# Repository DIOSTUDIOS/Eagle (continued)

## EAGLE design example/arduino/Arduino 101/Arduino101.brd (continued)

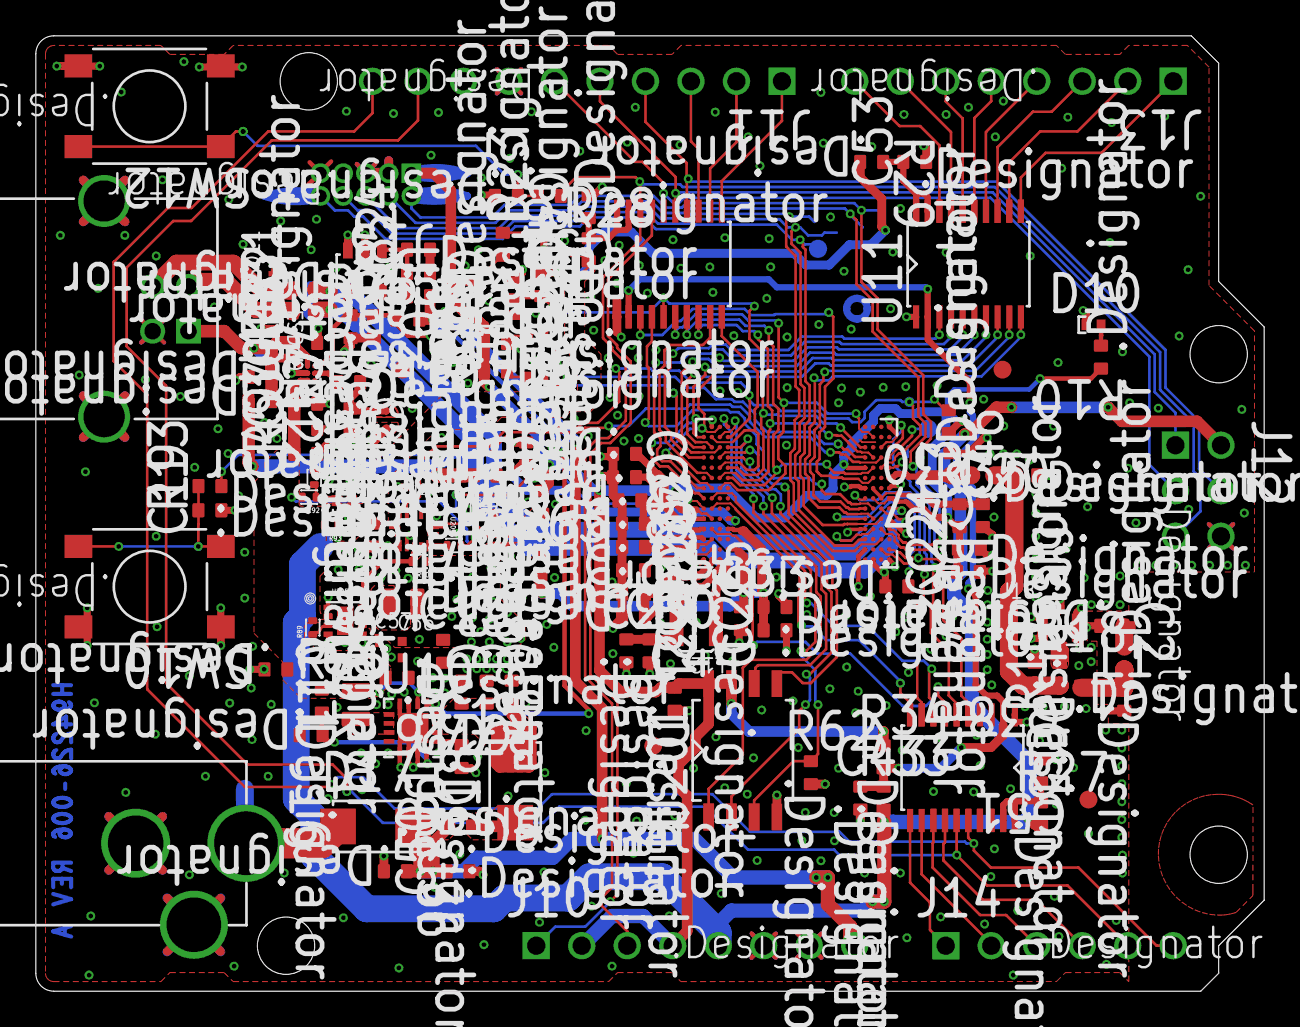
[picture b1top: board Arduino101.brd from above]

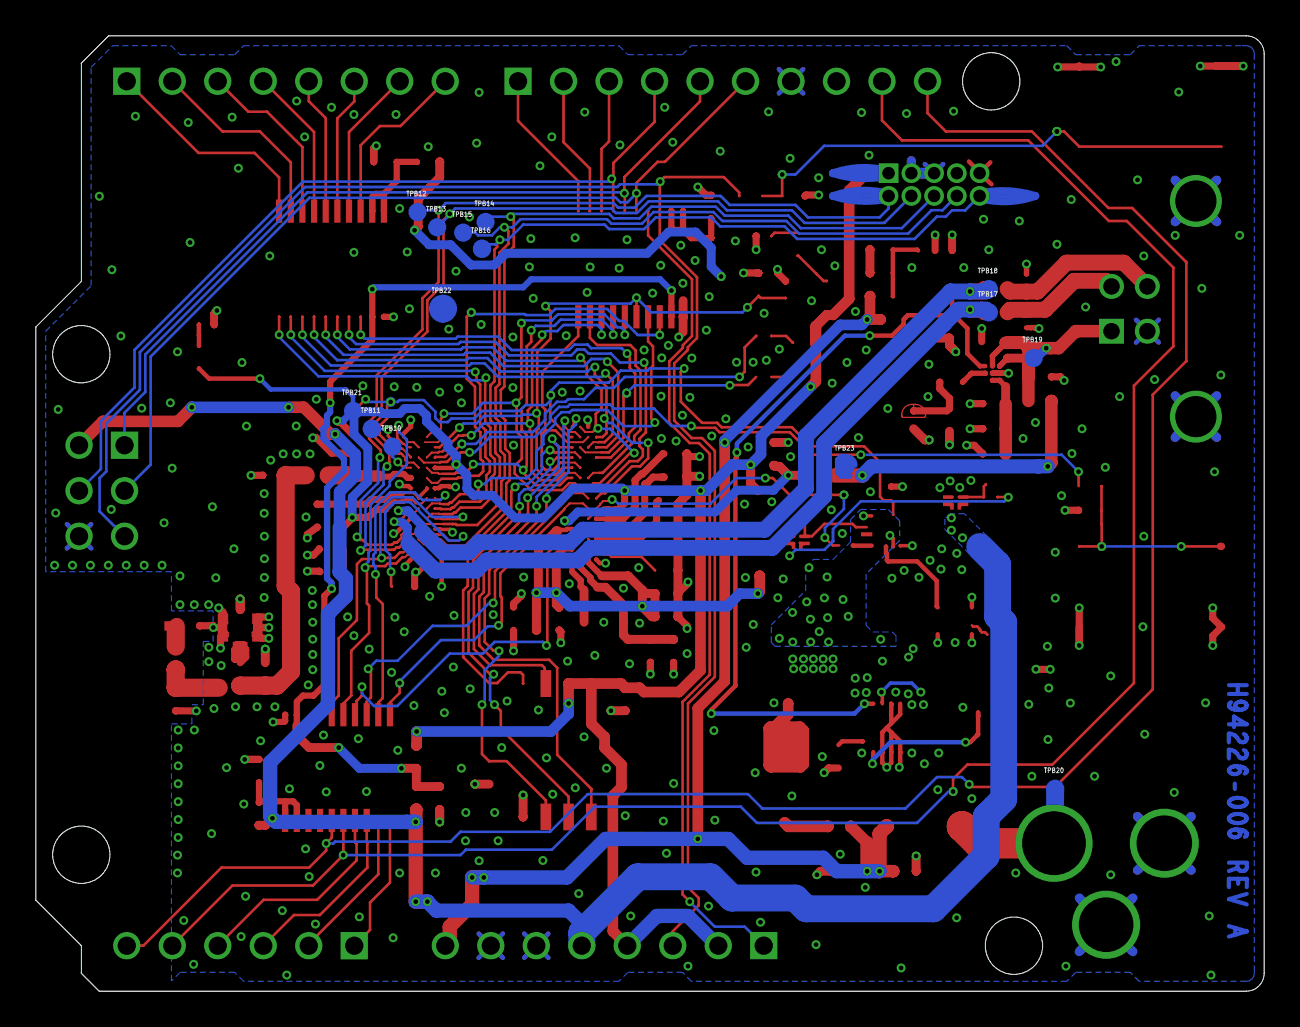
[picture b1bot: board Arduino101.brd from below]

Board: 6 copper layers, 68.6 x 53.3 mm, 146 parts (14 on the bottom side), 117 nets.

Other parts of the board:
DRILEGEND: DRILEGEND

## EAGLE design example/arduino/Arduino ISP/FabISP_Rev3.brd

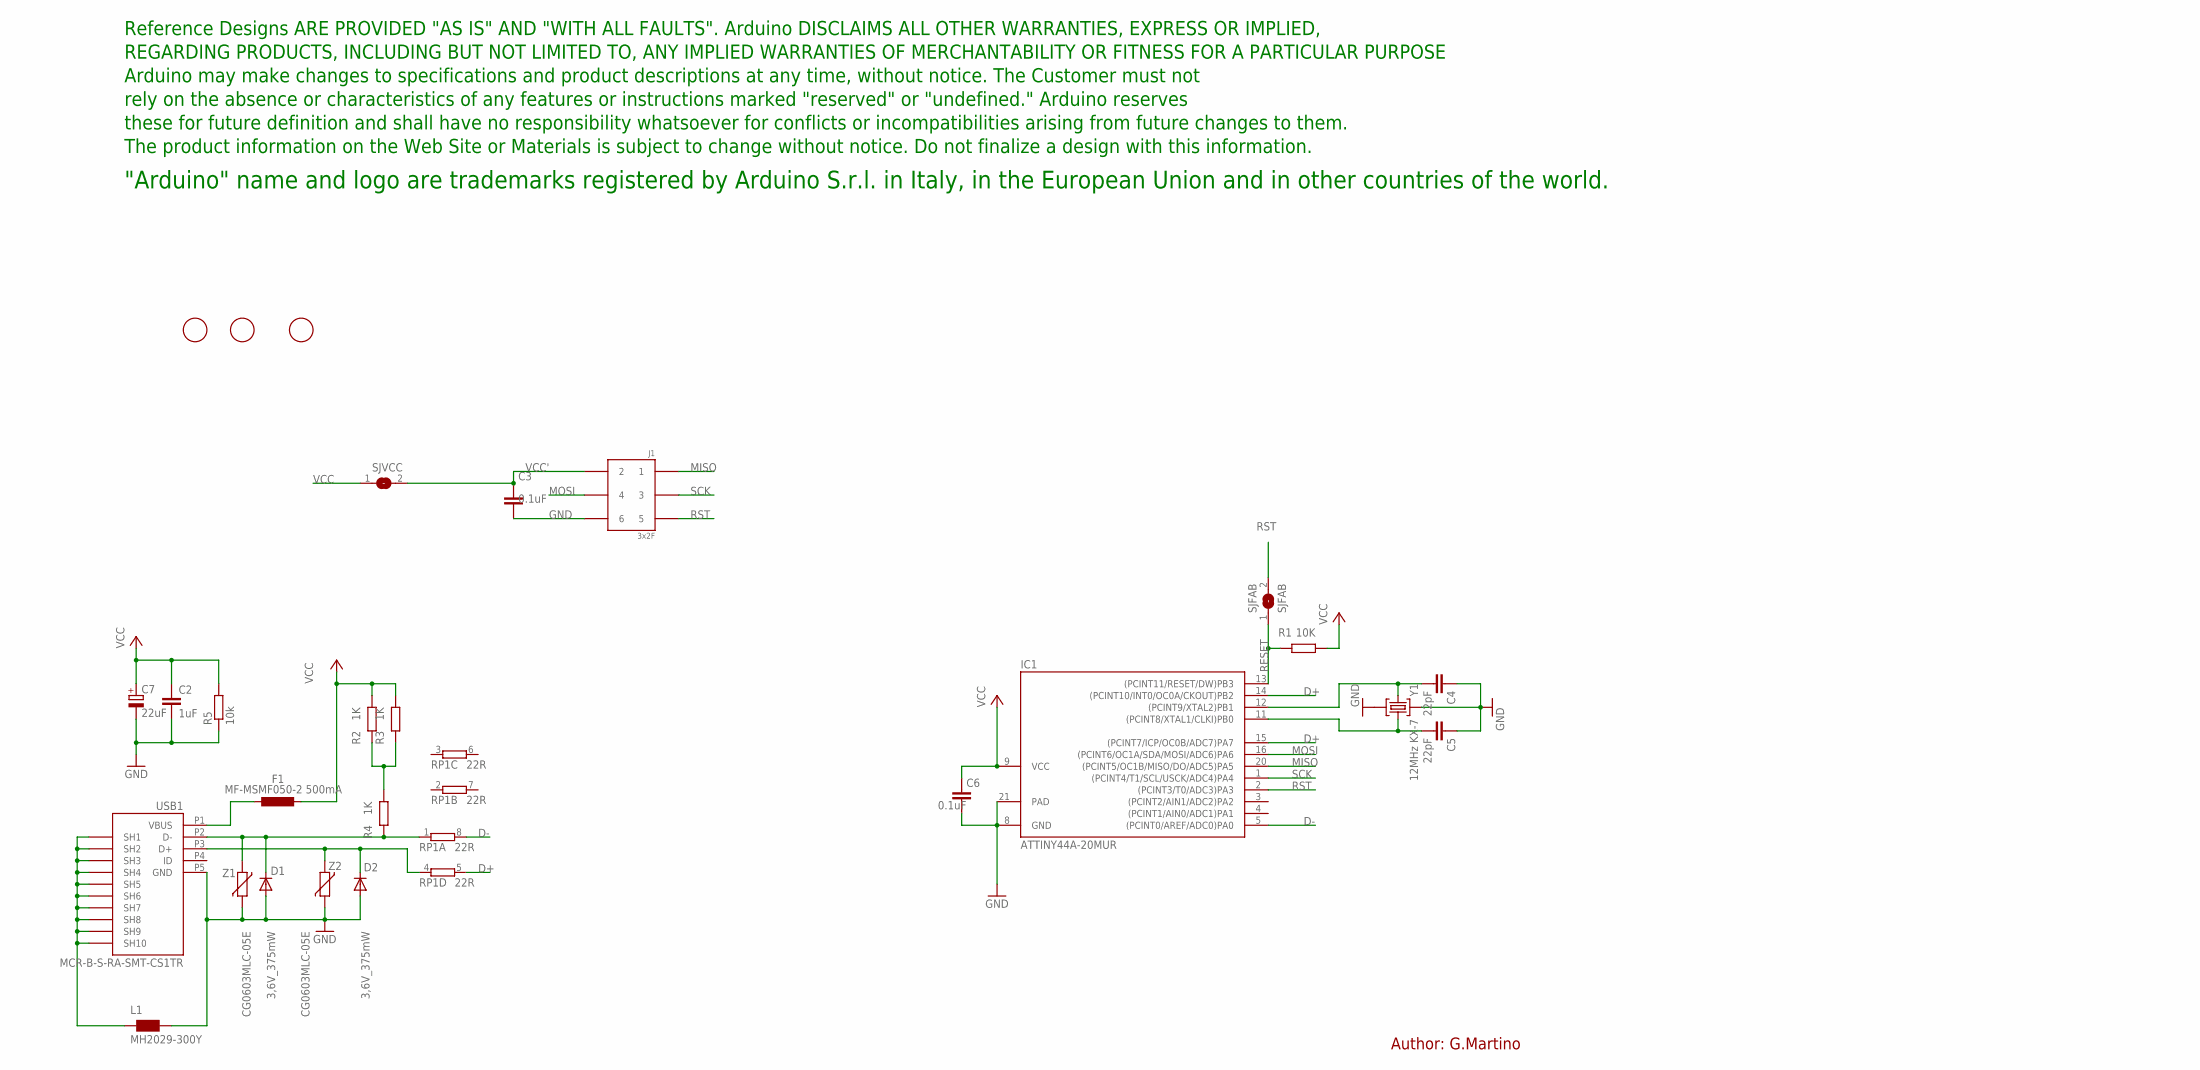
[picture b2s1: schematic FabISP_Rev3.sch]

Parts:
C2: 1uF; C0402
C3, C6: 0.1uF; C0402
C4, C5: 22pF; C0402
C7: 22uF; SMC_B
D1, D2: 3,6V_375mW; SOD123
F1: MF-MSMF050-2 500mA; L1812
IC1: ATTINY44A-20MUR; ATTINY24_44_84_QFN/MLF20
J1: 3x2F; HEAD3X2
L1: MH2029-300Y; 0805
R1: 10K; R0402
R2, R3, R4: 1K; R0402
R5: 10k; R0603-ROUND
RP1: 22R; CAY16
SJFAB: SJFAB
SJVCC: SJFAB
U$1, U$2, U$3: FIDUCIALMOUNT; FIDUCIA-MOUNT
U$5: DISCLAIMER
USB1: MCR-B-S-RA-SMT-CS1TR; CON2_USB_MICRO_B_AT
Y1: 12MHz KX-7; CRYSTAL-3.2-2.5
Z1, Z2: CG0603MLC-05E; CT/CN0603

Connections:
D+: IC1.14 ((PCINT10/INT0/OC0A/CKOUT)PB2), IC1.15 ((PCINT7/ICP/OC0B/ADC7)PA7), RP1.5 (2)
D-: IC1.5 ((PCINT0/AREF/ADC0)PA0), RP1.8 (2)
GND: C2.2, C3.2, C4.1, C5.1, C6.2, C7.-, D1.A, D2.A, IC1.8 (GND), IC1.21 (PAD), J1.6, L1.2, R5.1, USB1.P5 (GND), Y1.2 (GND), Y1.4 (GND), Z1.1, Z2.1
MISO: IC1.20 ((PCINT5/OC1B/MISO/DO/ADC5)PA5), J1.1
MOSI: IC1.16 ((PCINT6/OC1A/SDA/MOSI/ADC6)PA6), J1.4
unnamed: D1.C, R4.1, RP1.1, USB1.P2 (D-), Z1.2
unnamed: D2.C, RP1.4 (1), USB1.P3 (D+), Z2.2
unnamed: R2.1, R3.1, R4.2
unnamed: L1.1, USB1.P$1 (SH7), USB1.P$2 (SH8), USB1.P$3 (SH9), USB1.P$4 (SH10), USB1.P$5 (SH7), USB1.P$6 (SH8), USB1.P$7 (SH9), USB1.P$8 (SH10), USB1.S1 (SH1), USB1.S2 (SH2), USB1.S3 (SH3), USB1.S4 (SH4), USB1.S5 (SH5), USB1.S6 (SH6)
unnamed: F1.2, USB1.P1 (VBUS)
RESET: IC1.13 ((PCINT11/RESET/DW)PB3), R1.1, SJFAB.1
RST: IC1.2 ((PCINT3/T0/ADC3)PA3), J1.5, SJFAB.2
SCK: IC1.1 ((PCINT4/T1/SCL/USCK/ADC4)PA4), J1.3
VCC: C2.1, C6.1, C7.+, F1.1, IC1.9 (VCC), R1.2, R2.2, R3.2, R5.2, SJVCC.1
VCC': C3.1, J1.2, SJVCC.2
XTAL1: C4.2, IC1.12 ((PCINT9/XTAL2)PB1), Y1.3 (C2)
XTAL2: C5.2, IC1.11 ((PCINT8/XTAL1/CLKI)PB0), Y1.1 (C1)

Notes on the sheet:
Author: G.Martino

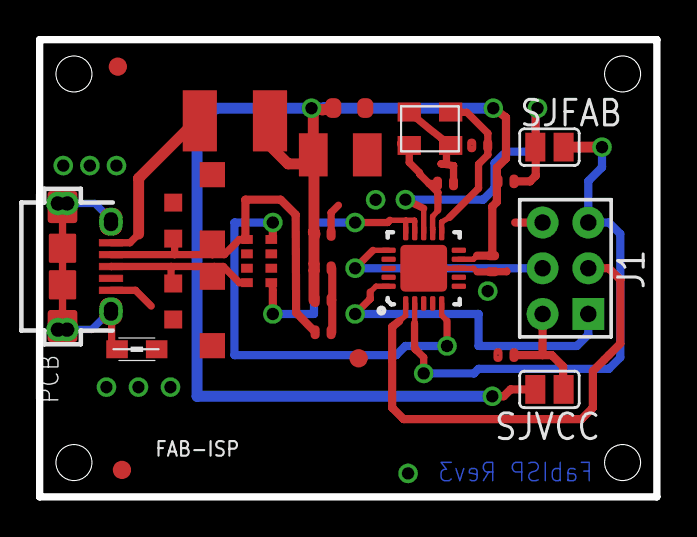
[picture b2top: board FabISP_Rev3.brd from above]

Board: 2 copper layers, 34.3 x 25.4 mm, 28 parts (0 on the bottom side), 17 nets.

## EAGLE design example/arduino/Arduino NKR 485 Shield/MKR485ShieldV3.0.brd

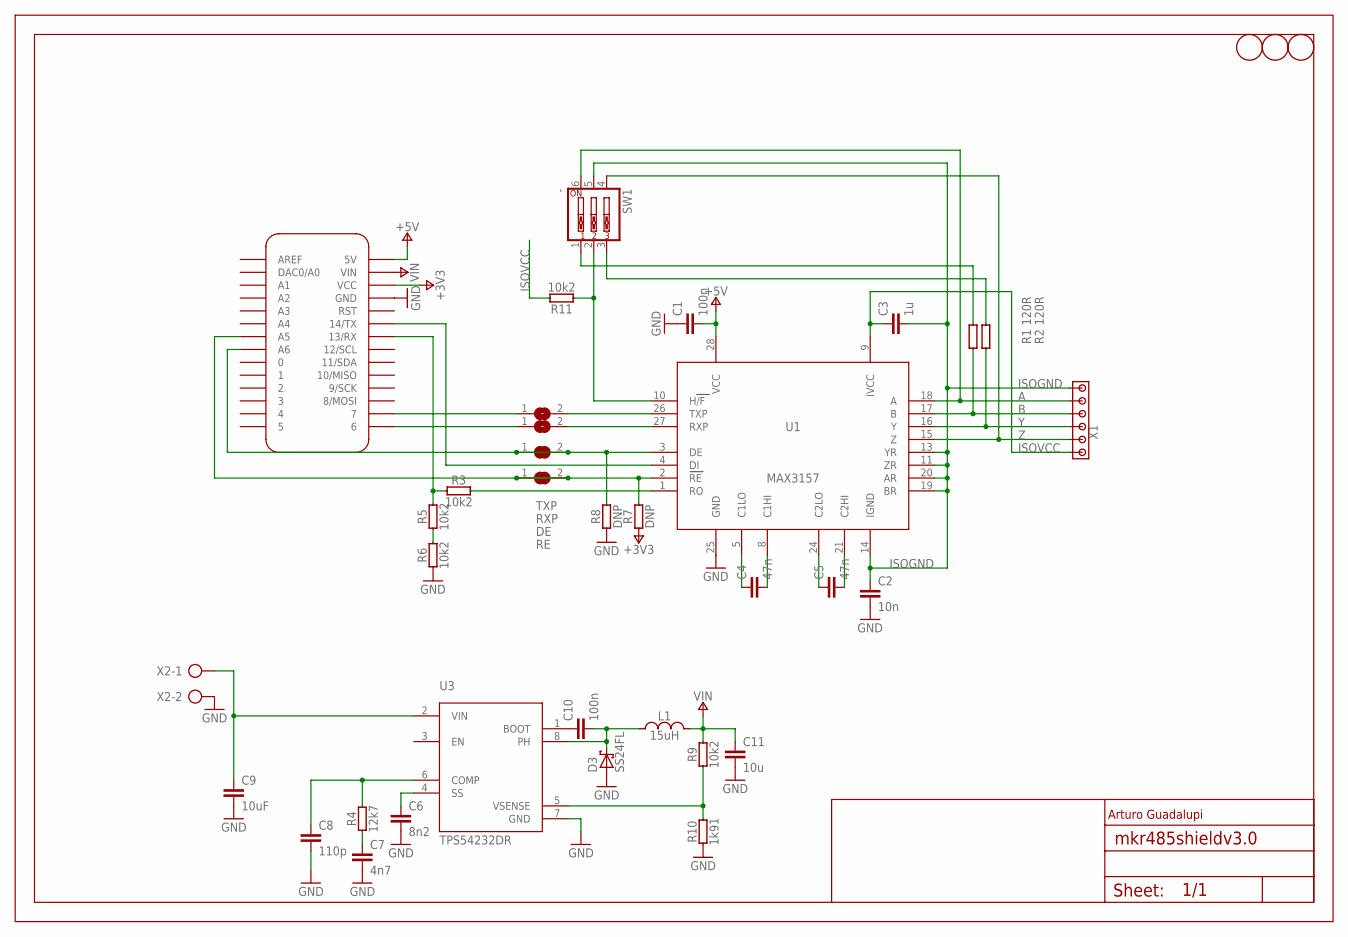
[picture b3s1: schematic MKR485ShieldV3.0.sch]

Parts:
C1, C10: 100n; 0402-1005X55N
C2: 10n; 0603-1608X90N
C3: 1u; 0603-1608X90N
C4, C5: 47n; 0402-1005X55N
C6: 8n2; 0402-1005X55N
C7: 4n7; 0402-1005X55N
C8: 110p; 0402-1005X55N
C9: 10uF; C1206
C11: 10u; 0603-1608X90N
D3: SS24FL; SOD123F
DE: DNP; SJ
FD1, FD2, FD3: DNP; FD-1-1.5
FRAME1: DNP; FRAME
L1: 15uH; SRN6045
MKR1: DNP; MKRBOARD-DIM
R1, R2: 120R; 0402-1005X55N
R3, R5, R6, R9, R11: 10k2; 0402-1005X55N
R4: 12k7; 0402-1005X55N
R7, R8: DNP; 0402-1005X55N
R10: 1k91; 0402-1005X55N
RE: DNP; SJ
RXP: DNP; SJ
SW1: -; EDG-03
TXP: DNP; SJ
U1: MAX3157; TSSOP28
U3: TPS54232DR; SO08
X1: -; SCREW6X2.54
X2: -; AK300/2

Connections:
+3V3: MKR1.VCC, R7.1
+5V: C1.2, MKR1.5V, U1.28 (VCC)
A: SW1.6, U1.18 (A), X1.5
B: R1.1, U1.17 (B), X1.4
DE: DE.1, DE.2, MKR1.A6, R8.2, U1.3 (DE)
GND: C1.1, C2.2, C6.2, C7.2, C8.2, C9.2, C11.2, D3.A, MKR1.GND, R6.1, R8.1, R10.1, U1.25 (GND), U3.7 (GND), X2.2
ISOGND: C2.1, C3.2, SW1.5, U1.11 (ZR), U1.13 (YR), U1.14 (IGND), U1.19 (BR), U1.20 (AR), X1.6
ISOVCC: C3.1, R11.2, U1.9 (IVCC), X1.1
unnamed: TXP.2, U1.26 (TXP)
unnamed: RXP.2, U1.27 (RXP)
unnamed: R11.1, SW1.2, U1.10 (H/F)
unnamed: R2.2, SW1.3
unnamed: MKR1.14 (14/TX), U1.4 (DI)
unnamed: C4.1, U1.5 (C1LO)
unnamed: C4.2, U1.8 (C1HI)
unnamed: C5.1, U1.24 (C2LO)
unnamed: C5.2, U1.21 (C2HI)
unnamed: C7.1, R4.1
unnamed: C8.1, R4.2, U3.6 (COMP)
unnamed: MKR1.13 (13/RX), R3.1, R5.2
unnamed: R1.2, SW1.1
unnamed: C6.1, U3.4 (SS)
unnamed: R3.2, U1.1 (RO)
unnamed: C9.1, U3.2 (VIN), X2.1
unnamed: C10.1, U3.1 (BOOT)
unnamed: C10.2, D3.C, L1.1, U3.8 (PH)
unnamed: R9.1, R10.2, U3.5 (VSENSE)
unnamed: R5.1, R6.2
RE: MKR1.A5, R7.2, RE.1, RE.2, U1.2 (RE)
RXP: MKR1.6, RXP.1
TXP: MKR1.7, TXP.1
VIN: C11.1, L1.2, MKR1.VIN, R9.2
Y: R2.1, U1.16 (Y), X1.3
Z: SW1.4, U1.15 (Z), X1.2

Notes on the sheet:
Arturo Guadalupi

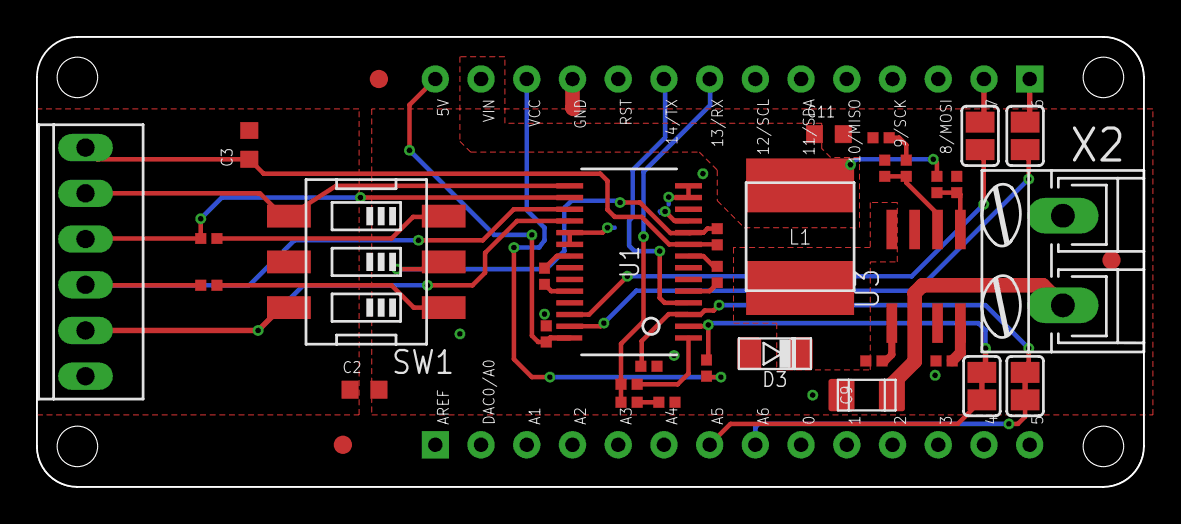
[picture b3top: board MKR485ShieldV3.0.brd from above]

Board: 2 copper layers, 61.5 x 25.0 mm, 38 parts (0 on the bottom side), 34 nets.

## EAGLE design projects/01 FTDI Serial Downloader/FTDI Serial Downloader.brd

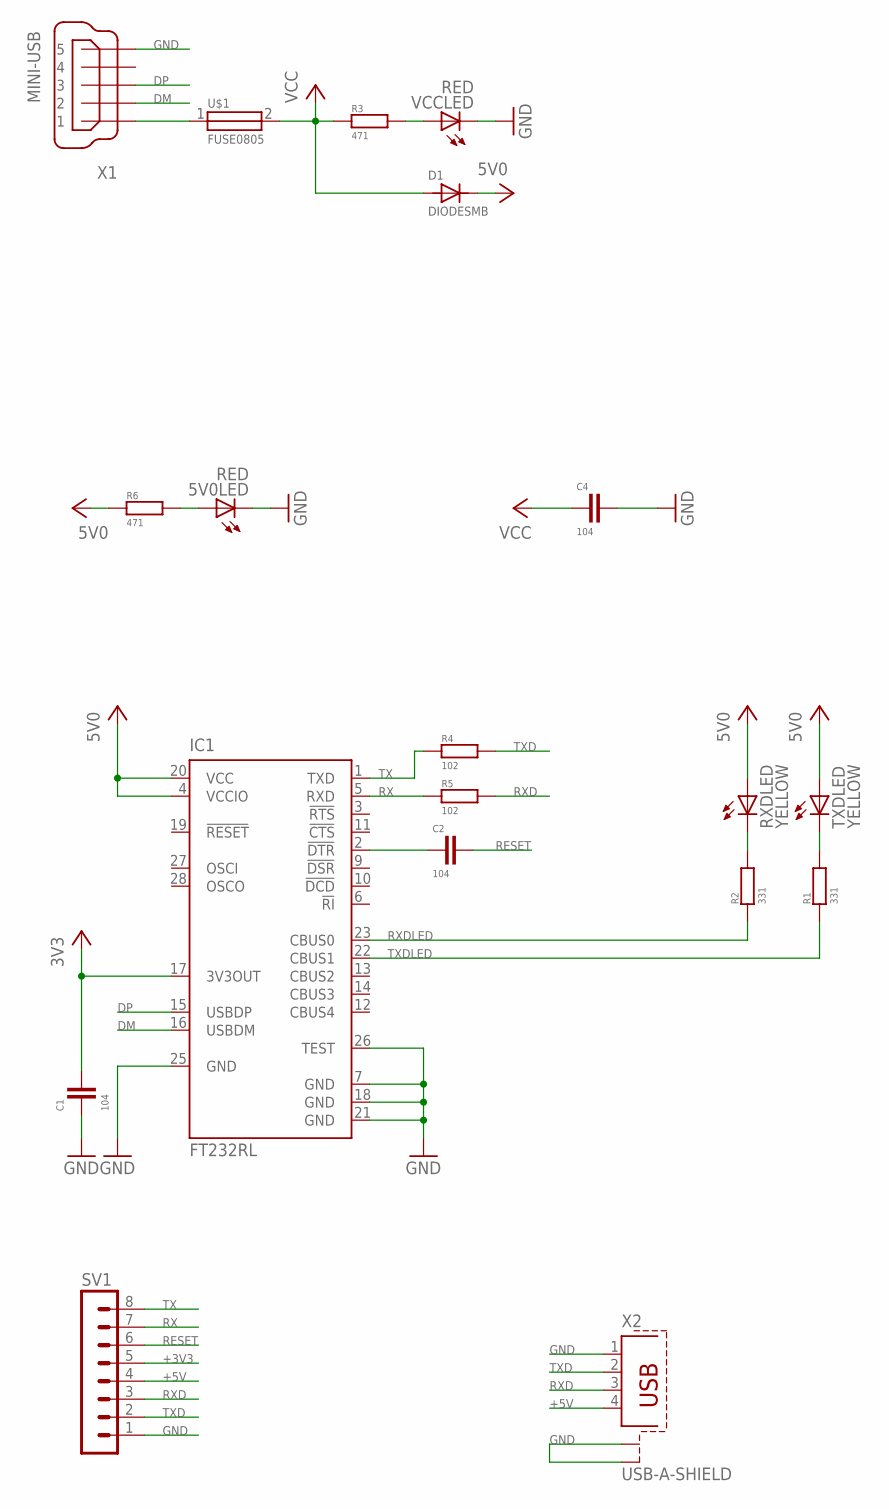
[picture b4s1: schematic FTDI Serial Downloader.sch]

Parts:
5V0LED: RED; CHIPLED_0805
C1, C2, C4: 104; C0805
D1: DIODESMB; SMB
IC1: FT232RL; SSOP28
R1, R2: 331; R0805
R3, R6: 471; R0805
R4, R5: 102; R0805
RXDLED: YELLOW; CHIPLED_0805
SV1: MA08-1
TXDLED: YELLOW; CHIPLED_0805
U$1: FUSE0805; F0805
VCCLED: RED; CHIPLED_0805
X1: MINI-USB; 32005-201
X2: USB-A-SHIELD

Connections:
+3V3: C1.1, IC1.17 (3V3OUT), SV1.5
+5V: D1.1, IC1.4 (VCCIO), IC1.20 (VCC), R6.1, RXDLED.A, SV1.4, TXDLED.A, X2.4
DM: IC1.16 (USBDM), X1.2
DP: IC1.15 (USBDP), X1.3
GND: 5V0LED.C, C1.2, C4.1, IC1.7 (GND), IC1.18 (GND), IC1.21 (GND), IC1.25 (GND), IC1.26 (TEST), SV1.1, VCCLED.C, X1.5, X2.1, X2.S1, X2.S2
unnamed: R2.2, RXDLED.C
unnamed: U$1.1, X1.1
unnamed: R1.2, TXDLED.C
unnamed: R3.2, VCCLED.A
unnamed: C2.2, IC1.2 (!DTR)
unnamed: 5V0LED.A, R6.2
RESET: C2.1, SV1.6
RX: IC1.5 (RXD), R5.1, SV1.7
RXD: R5.2, SV1.3, X2.3
RXDLED: IC1.23 (CBUS0), R2.1
TX: IC1.1 (TXD), R4.1, SV1.8
TXD: R4.2, SV1.2, X2.2
TXDLED: IC1.22 (CBUS1), R1.1
VCC: C4.2, D1.2, R3.1, U$1.2

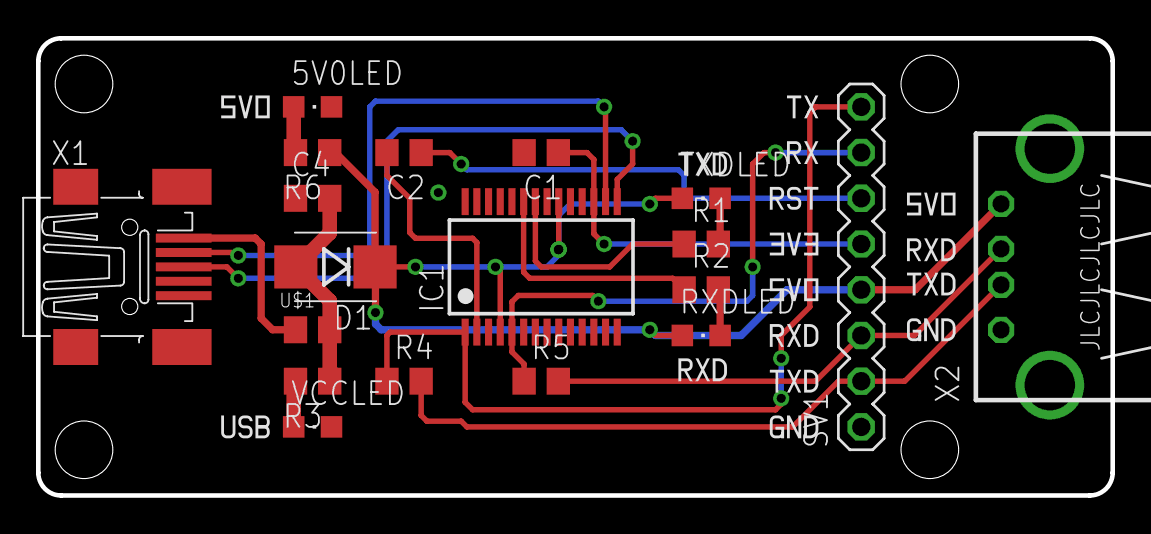
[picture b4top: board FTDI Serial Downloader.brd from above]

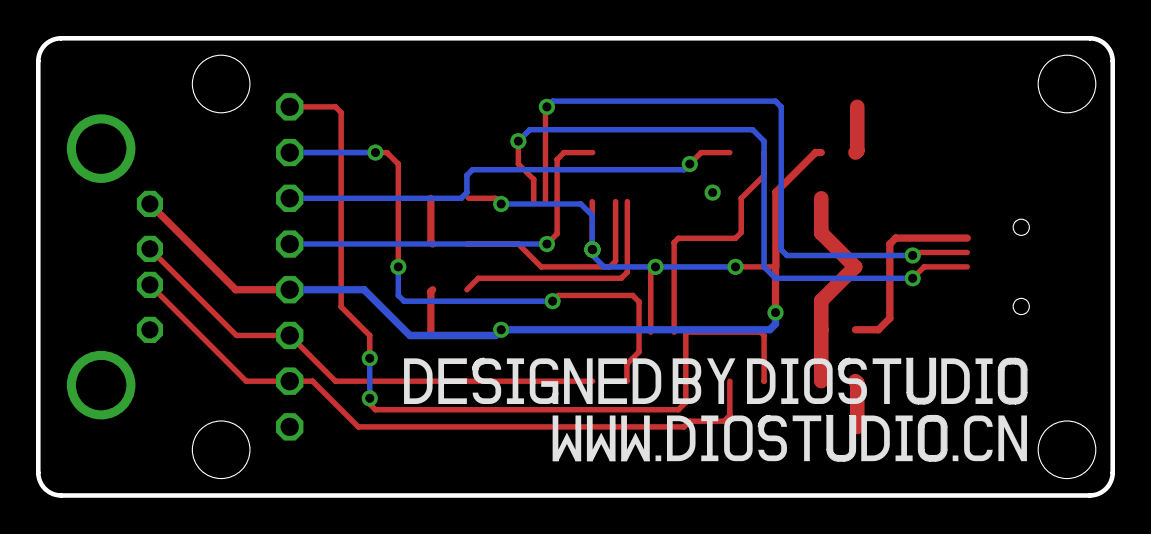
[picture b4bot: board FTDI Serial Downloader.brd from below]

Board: 2 copper layers, 59.7 x 25.4 mm, 37 parts (2 on the bottom side), 19 nets.

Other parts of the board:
U$2: TX_050
U$3: RX_050
U$4: 3V3_050
U$5, U$12, U$16: 5V0_050
U$6, U$11, U$14: RXD_050
U$7, U$10, U$15: TXD_050
U$8, U$13: GND_050
U$9: RST_050
U$17: USB_050
U$18: INFO_100
U$19: WEB_100

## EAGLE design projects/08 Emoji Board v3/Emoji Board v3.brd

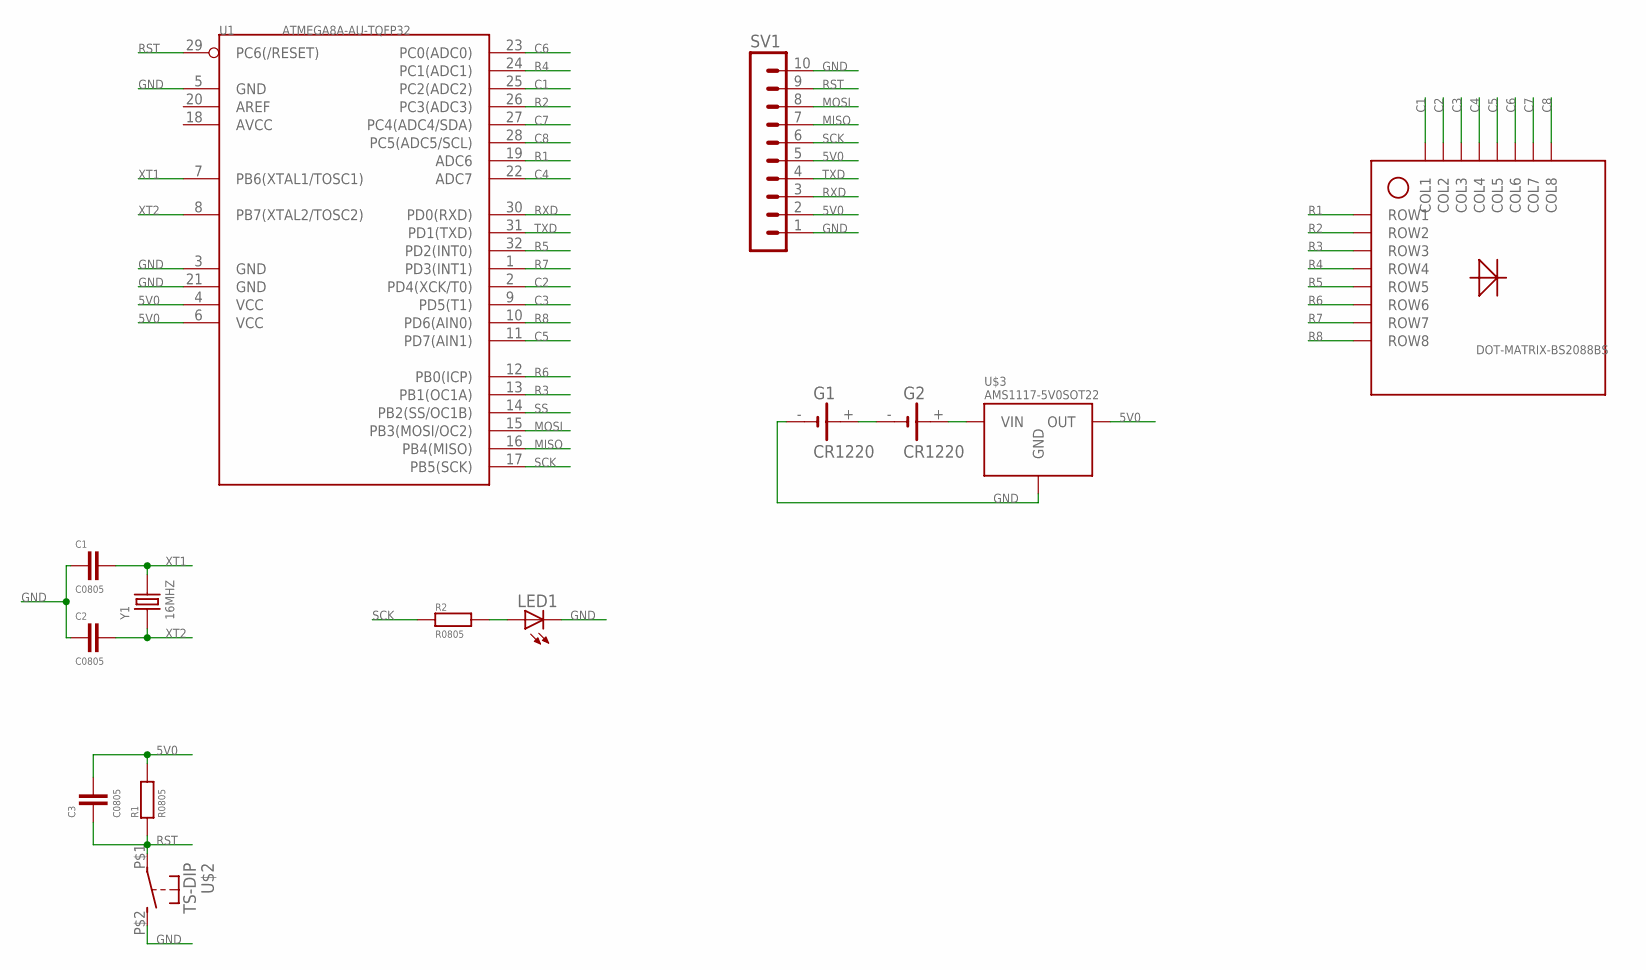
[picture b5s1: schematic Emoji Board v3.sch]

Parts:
C1, C2, C3: C0805
G1, G2: CR1220
LED1: LEDCHIPLED_0805; LED0805
R1, R2: R0805
SV1: MA10-1W
U1: ATMEGA8A-AU-TQFP32; TQFP32
U$1: DOT-MATRIX-BS2088BS; 2088BS
U$2: TS-DIP
U$3: AMS1117-5V0SOT22; SOT223
Y1: 16MHZ; HC49US

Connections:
5V0: C3.1, R1.2, SV1.2, SV1.5, U1.4 (VCC), U1.6 (VCC), U$3.OUT
C1: U1.25 (PC2(ADC2)), U$1.COL1
C2: U1.2 (PD4(XCK/T0)), U$1.COL2
C3: U1.9 (PD5(T1)), U$1.COL3
C4: U1.22 (ADC7), U$1.COL4
C5: U1.11 (PD7(AIN1)), U$1.COL5
C6: U1.23 (PC0(ADC0)), U$1.COL6
C7: U1.27 (PC4(ADC4/SDA)), U$1.COL7
C8: U1.28 (PC5(ADC5/SCL)), U$1.COL8
GND: C1.2, C2.2, G1.-, LED1.C, SV1.1, SV1.10, U1.3 (GND), U1.5 (GND), U1.21 (GND), U$2.P$2 (S), U$3.GND
MISO: SV1.7, U1.16 (PB4(MISO))
MOSI: SV1.8, U1.15 (PB3(MOSI/OC2))
unnamed: LED1.A, R2.2
unnamed: G1.+, G2.-
unnamed: G2.+, U$3.VIN
R1: U1.19 (ADC6), U$1.ROW1
R2: U1.26 (PC3(ADC3)), U$1.ROW2
R3: U1.13 (PB1(OC1A)), U$1.ROW3
R4: U1.24 (PC1(ADC1)), U$1.ROW4
R5: U1.32 (PD2(INT0)), U$1.ROW5
R6: U1.12 (PB0(ICP)), U$1.ROW6
R7: U1.1 (PD3(INT1)), U$1.ROW7
R8: U1.10 (PD6(AIN0)), U$1.ROW8
RST: C3.2, R1.1, SV1.9, U1.29 (PC6(/RESET)), U$2.P$1
RXD: SV1.3, U1.30 (PD0(RXD))
SCK: R2.1, SV1.6, U1.17 (PB5(SCK))
SS: U1.14 (PB2(SS/OC1B))
TXD: SV1.4, U1.31 (PD1(TXD))
XT1: C1.1, U1.7 (PB6(XTAL1/TOSC1)), Y1.2
XT2: C2.1, U1.8 (PB7(XTAL2/TOSC2)), Y1.1

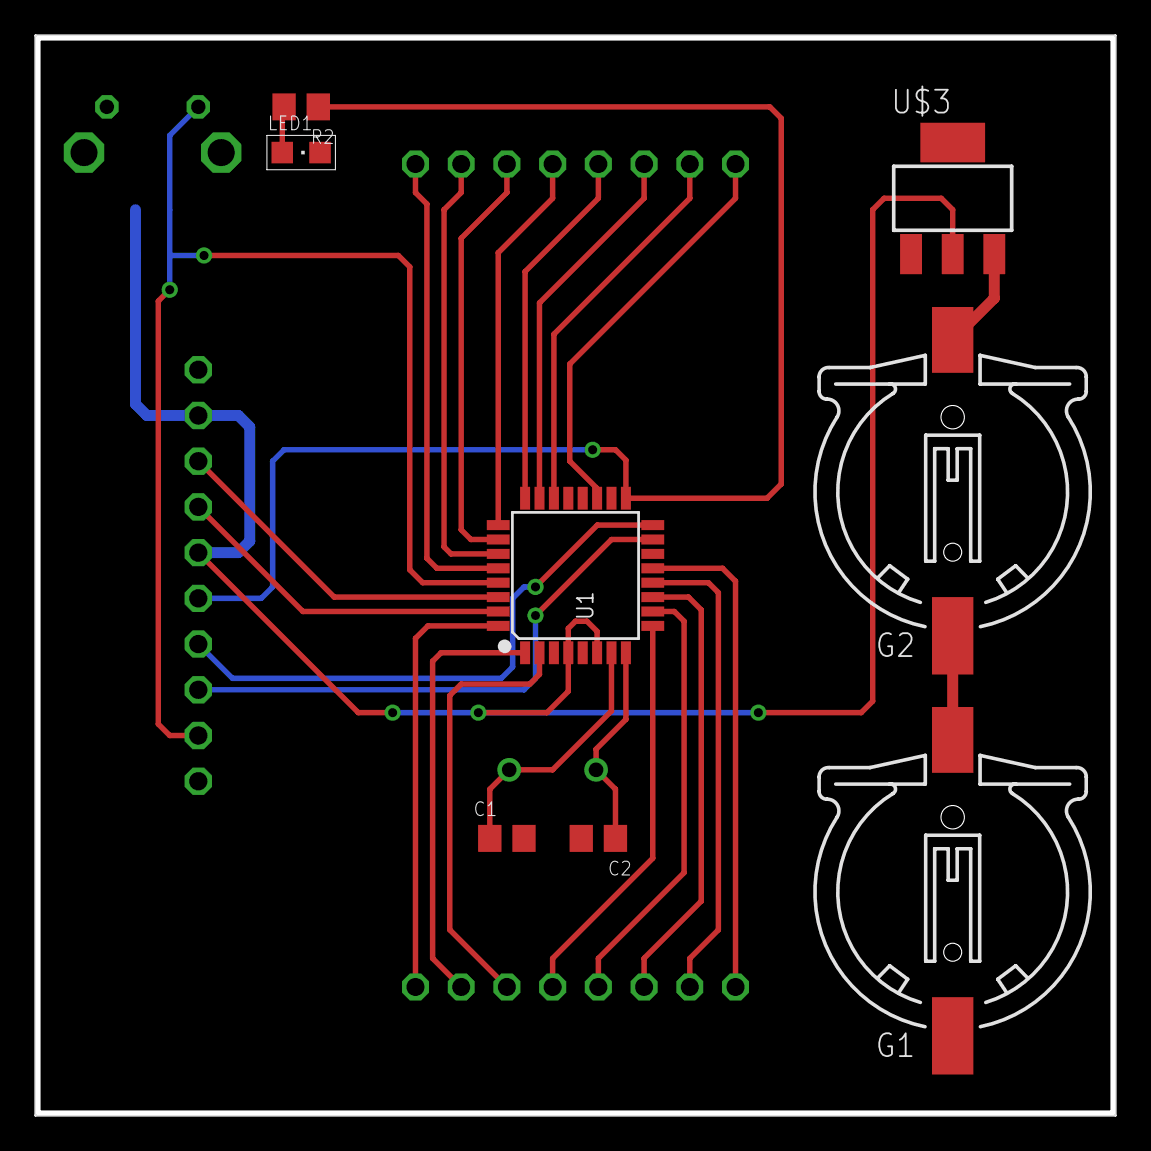
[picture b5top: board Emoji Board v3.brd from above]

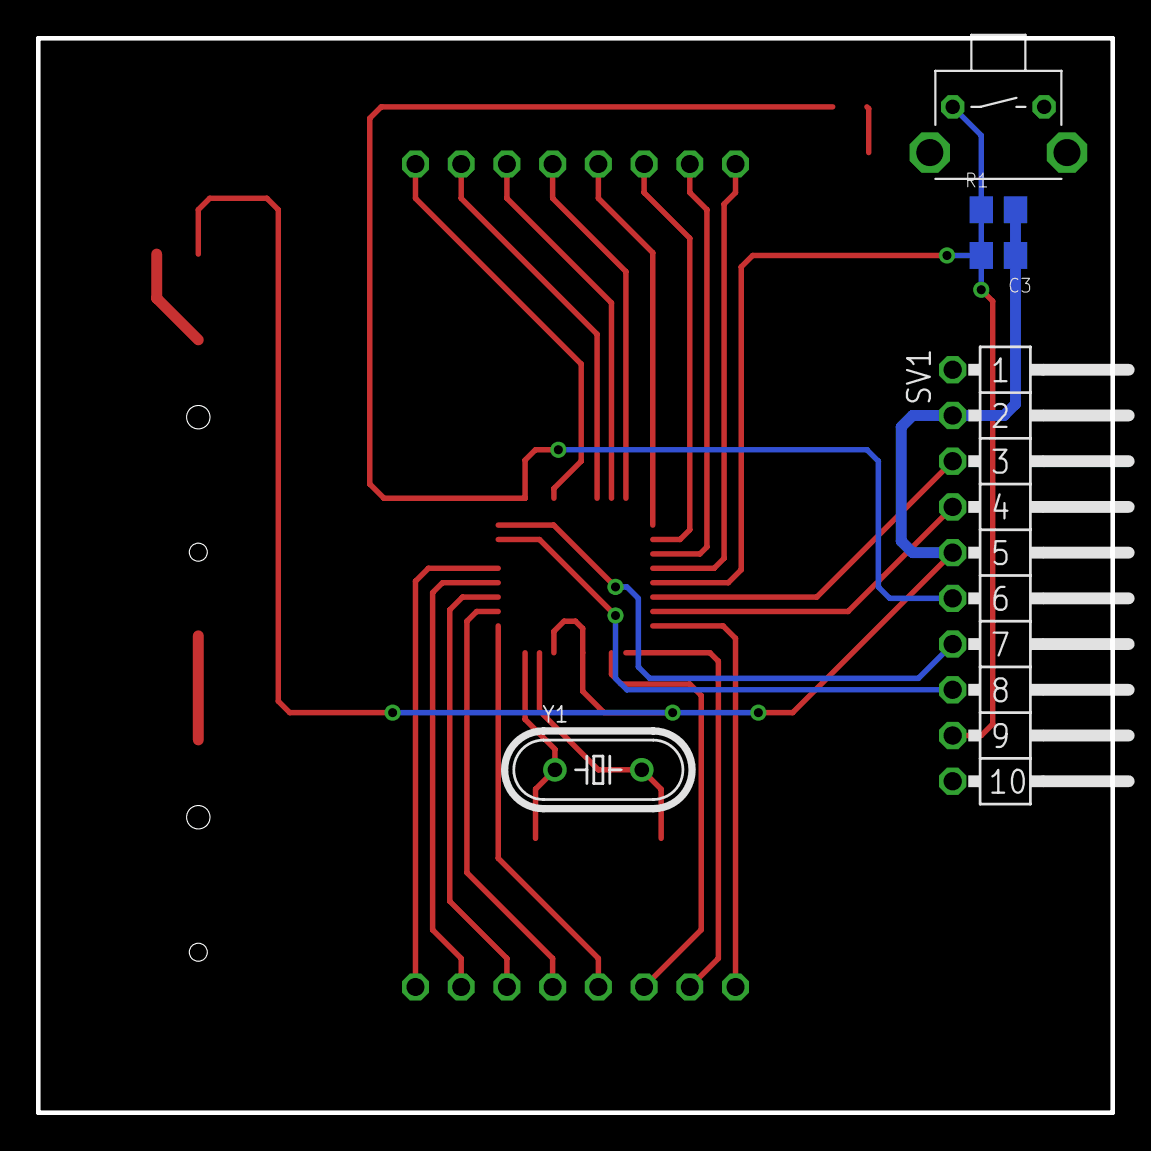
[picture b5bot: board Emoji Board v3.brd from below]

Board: 2 copper layers, 59.7 x 59.7 mm, 14 parts (5 on the bottom side), 29 nets.

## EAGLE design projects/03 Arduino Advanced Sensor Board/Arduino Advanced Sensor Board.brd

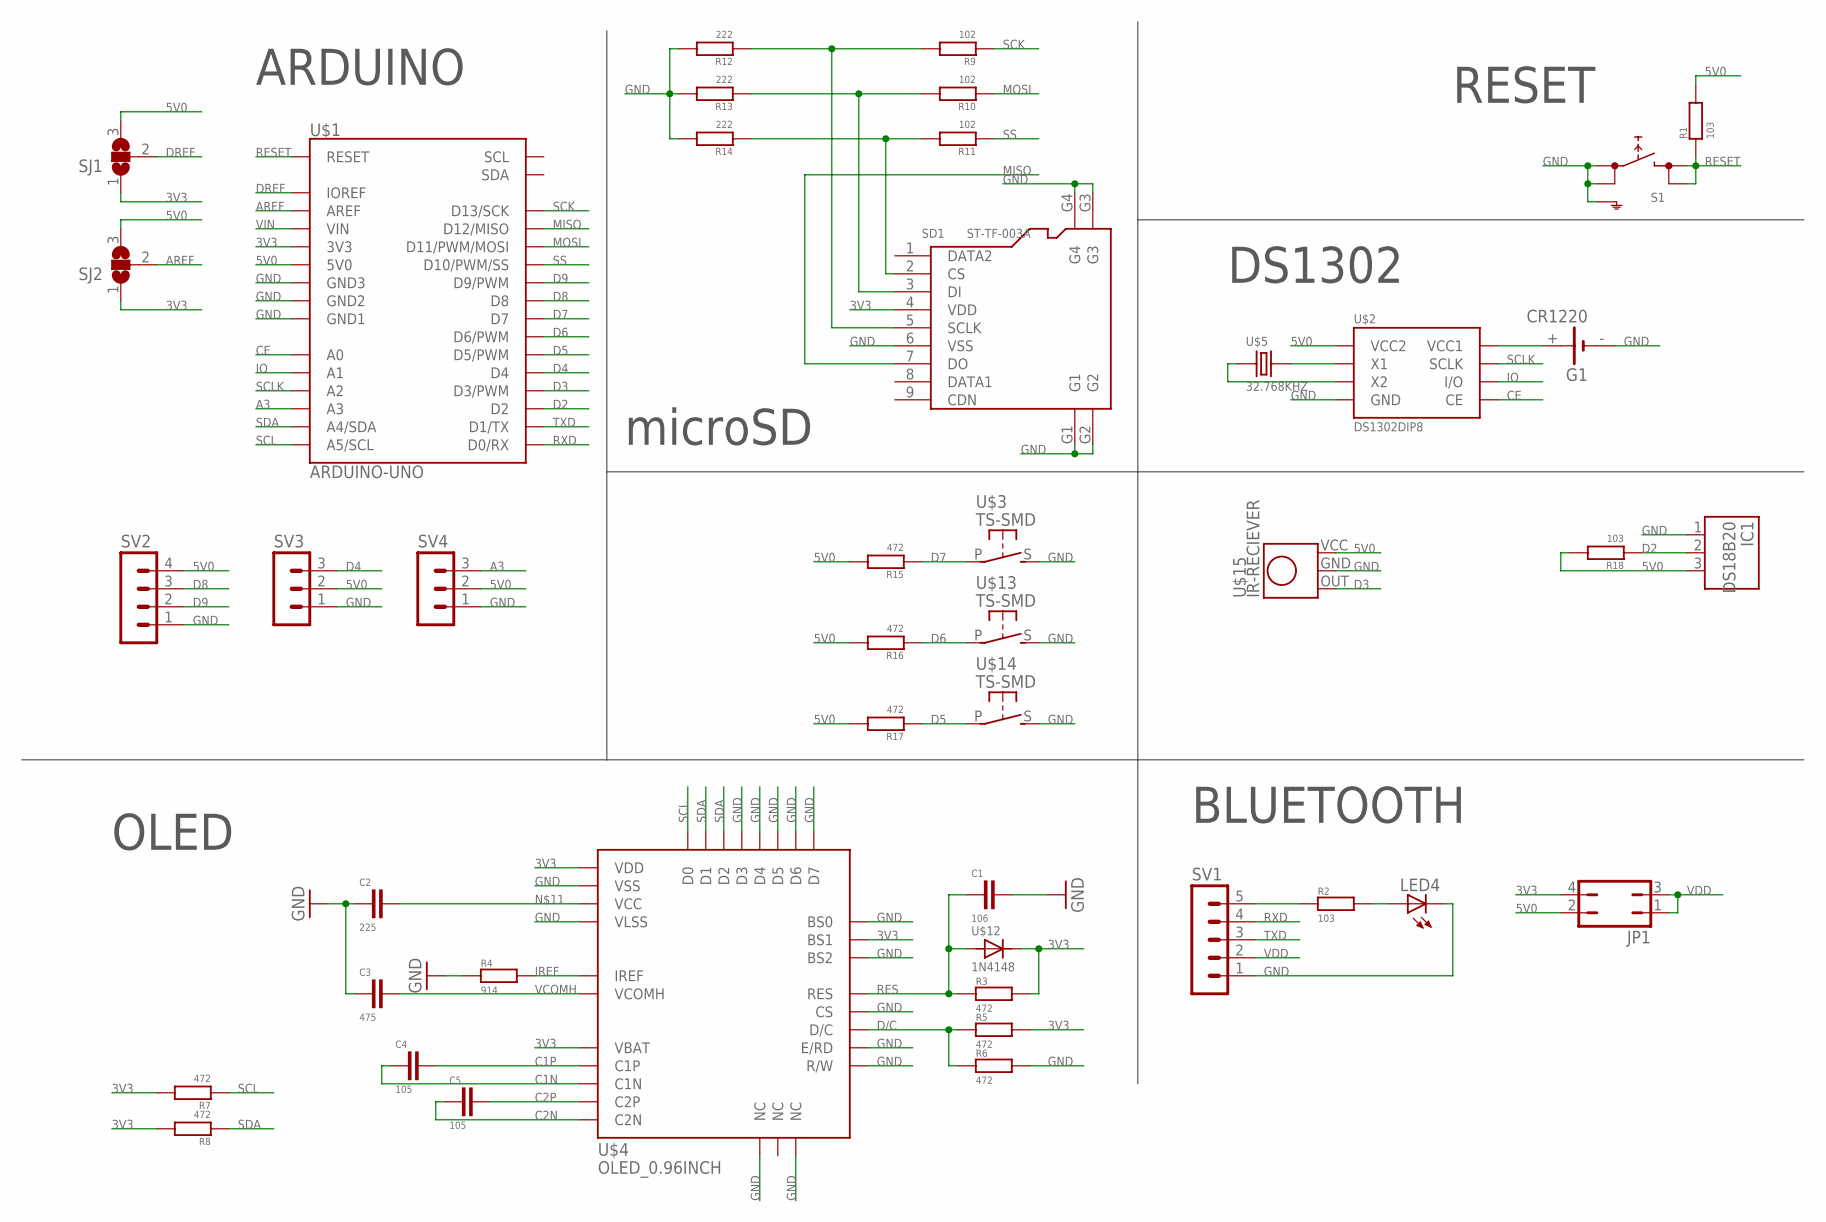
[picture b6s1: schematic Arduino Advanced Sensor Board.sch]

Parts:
C1: 106; C0805
C2: 225; C0805
C3: 475; C0805
C4, C5: 105; C0805
G1: CR1220
IC1: DS18B20; TO92
JP1: JP2Q
LED4: LEDCHIPLED_0805; LED0805
R1, R2, R18: 103; R0805
R3, R5, R6, R7, R8, R15, R16, R17: 472; R0805
R4: 914; R0805
R9, R10, R11: 102; R0805
R12, R13, R14: 222; R0805
S1: TS-SMD_6S6_SHIELD; TS-SMD_6*6_SHIELD
SD1: ST-TF-003A; MICRO-SD-SMD-9+4
SJ1, SJ2: SJ2W; SJ_2
SV1: MA05-1
SV2: MA04-1
SV3, SV4: MA03-1
U$1: ARDUINO-UNO
U$2: DS1302DIP8; DIP8
U$3, U$13, U$14: TS-SMD
U$4: OLED_0.96INCH
U$5: 32.768KHZ
U$12: 1N4148; SOD123
U$15: IR-RECIEVER

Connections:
3V3: JP1.4, R3.2, R5.2, R7.2, R8.2, SD1.4 (VDD), SJ1.1, SJ2.1, U$1.3V3, U$4.6 (VBAT), U$4.9 (VDD), U$4.11 (BS1), U$12.1
5V0: IC1.3 (VCC), JP1.2, R1.2, R15.2, R16.2, R17.2, R18.2, SJ1.3, SJ2.3, SV2.4, SV3.2, SV4.2, U$1.5V0, U$2.1 (VCC2), U$15.VCC
A3: SV4.3, U$1.A3
AREF: SJ2.2, U$1.AREF
C1N: C4.2, U$4.5 (C1N)
C1P: C4.1, U$4.4 (C1P)
C2N: C5.2, U$4.3 (C2N)
C2P: C5.1, U$4.2 (C2P)
CE: U$1.A0, U$2.5 (CE)
D2: IC1.2 (DQ), R18.1, U$1.D2
D3: U$1.D3 (D3/PWM), U$15.OUT
D4: SV3.3, U$1.D4
D5: R17.1, U$1.D5 (D5/PWM), U$14.P
D6: R16.1, U$1.D6 (D6/PWM), U$13.P
D7: R15.1, U$1.D7, U$3.P
D8: SV2.3, U$1.D8
D9: SV2.2, U$1.D9 (D9/PWM)
D/C: R5.1, R6.1, U$4.15 (D/C)
DREF: SJ1.2, U$1.REF (IOREF)
GND: C1.1, C2.2, C3.2, G1.-, IC1.1 (GND), LED4.C, R4.1, R6.2, R12.2, R13.2, R14.2, S1.1 (1.1), S1.2 (1.2), S1.5 (SH), SD1.6 (VSS), SD1.G1, SD1.G2, SD1.G3, SD1.G4, SV1.1, SV2.1, SV3.1, SV4.1, U$1.GND1, U$1.GND2, U$1.GND3, U$2.4 (GND), U$3.S, U$4.1 (NC), U$4.8 (VSS), U$4.10 (BS0), U$4.12 (BS2), U$4.13 (CS), U$4.16 (R/W), U$4.17 (E/RD), U$4.21 (D3), U$4.22 (D4), U$4.23 (D5), U$4.24 (D6), U$4.25 (D7), U$4.29 (VLSS), U$4.30 (NC), U$13.S, U$14.S, U$15.GND
IO: U$1.A1, U$2.6 (I/O)
IREF: R4.2, U$4.26 (IREF)
MISO: SD1.7 (DO), U$1.D12 (D12/MISO)
MOSI: R10.1, U$1.D11 (D11/PWM/MOSI)
unnamed: U$2.2 (X1), U$5.P$2 (2)
unnamed: U$2.3 (X2), U$5.P$1 (1)
unnamed: G1.+, U$2.8 (VCC1)
unnamed: R2.1, SV1.5
unnamed: LED4.A, R2.2
unnamed: R11.2, R14.1, SD1.2 (CS)
unnamed: R10.2, R13.1, SD1.3 (DI)
unnamed: C2.1, U$4.28 (VCC)
unnamed: R9.2, R12.1, SD1.5 (SCLK)
RES: C1.2, R3.1, U$4.14 (RES), U$12.2
RESET: R1.1, S1.3 (2.1), S1.4 (2.2), U$1.RST (RESET)
RXD: SV1.4, U$1.D0 (D0/RX)
SCK: R9.1, U$1.D13 (D13/SCK)
SCL: R7.1, U$1.A5 (A5/SCL), U$4.18 (D0)
SCLK: U$1.A2, U$2.7 (SCLK)
SDA: R8.1, U$1.A4 (A4/SDA), U$4.19 (D1), U$4.20 (D2)
SS: R11.1, U$1.D10 (D10/PWM/SS)
TXD: SV1.3, U$1.D1 (D1/TX)
VCOMH: C3.1, U$4.27 (VCOMH)
VDD: JP1.1, JP1.3, SV1.2
VIN: U$1.VIN

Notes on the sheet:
OLED
DS1302
BLUETOOTH
RESET
ARDUINO
microSD
